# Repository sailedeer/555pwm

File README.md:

PCB schematic and layout which uses a 555 Timer to generate an adjustable PWM signal.

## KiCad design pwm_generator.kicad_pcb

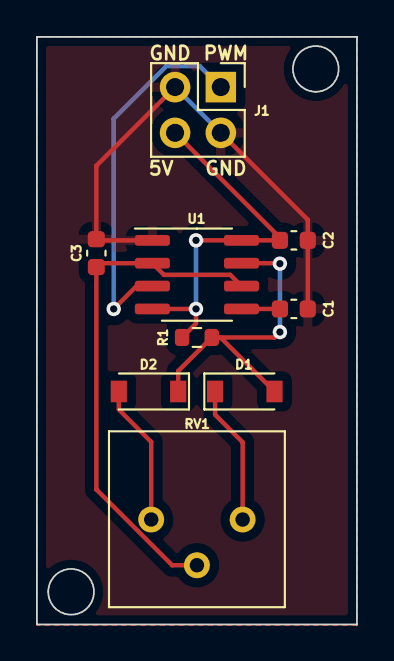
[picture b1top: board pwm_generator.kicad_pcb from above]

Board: 2 copper layers, 17.8 x 32.6 mm, 9 parts (0 on the bottom side), 8 nets.

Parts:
C1: 0.01u; C_0603_1608Metric
C2: 0.1u; C_0603_1608Metric
C3: 47u; C_0603_1608Metric
D1, D2: D_Small; D_SOD-123
J1: Conn_02x02_Counter_Clockwise; PinHeader_2x02_P2.54mm_Vertical
R1: 1k; R_0603_1608Metric
RV1: 5k; Potentiometer_Bourns_3386P_Vertical
U1: SA555D; SOIC-8_3.9x4.9mm_P1.27mm

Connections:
+5V: C2.2, J1.4, R1.1, U1.4 (R), U1.8 (VCC)
/OUT: J1.1, U1.3 (Q)
/TR: C3.2, RV1.2, U1.2 (TR), U1.6 (THR)
GND: C1.2, C2.1, C3.1, J1.2, J1.3, U1.1 (GND)
unnamed: C1.1, U1.5 (CV)
unnamed: D1.1 (K), RV1.3
unnamed: D1.2 (A), D2.1 (K), R1.2, U1.7 (DIS)
unnamed: D2.2 (A), RV1.1

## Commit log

2022-02-05 added some auto-generated files
2022-02-05 added project files
2022-02-05 first crack at circuit schematic
2022-02-25 update freq
2022-03-14 rev 1 pcb layout
